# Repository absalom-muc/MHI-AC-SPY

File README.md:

# MHI-AC-SPY

**This repository is no longer maintained and is therefore archived. An improved version including writing to the air conditioner is [here](https://github.com/absalom-muc/MHI-AC-Ctrl)**

The version here should be only used as a demonstration how to program the HW SPI of the ESP8266 for receiving data.

The program reads data (e.g. room temperature, fan status etc.) from a Mitsubishi Heavy Industries (MHI)
air conditioner (AC) via SPI and sends the data via MQTT. The AC is the SPI master and the ESP8266 is the SPI slave.
So far only reading from the AC is supported. (but writing is planned for the future)
The program has a draft status and your input is welcome.
My target is to read and write data with an ESP8266.

# Attention:
You have to open the indoor unit to have access to the SPI. Opening of the indoor unit should be done by 
a qualified professional because faulty handling may cause leakage of water, electric shock or fire!

# Prerequisites:
For use of the program you have to connect your ESP8266 (I use a LOLIN(WEMOS) D1 R2 & mini with 80 MHz) via a
cable connector to your air conditioner. This has to be a split device (separated indoor and outdoor unit).
I assume that all indoor units of the type SRC xx ZS-S are supported. I use the indoor unit SRK 35 ZS-S and the outdoor unit SRC 35 ZS-S.
  
# Installing:

## Hardware:
The ESP8266 is powered from the AC via DC-DC (12V -> 5V) converter
The ESP8266 SPI signals SCL (SPI clock) and MOSI (Master Out Slave In) signals are connected via a voltage divider with the AC. But after gaining some experiences I recommend to use a voltage level shifter instead of a voltage divider.

## Software:
The program uses the [MQTT client library](https://github.com/knolleary/pubsubclient) from Nick O'Leary (knolleary). Thank you Nick - great work!
Please check his GitHub page to see how to install it.
Dwonload MHI-SPI.ino and adapt ssid, password and the MQTT server data in the row MQTTclient.setServer("ds218p", 1883);

# License
This project is licensed under the MIT License - see the LICENSE.md file for details

# Acknowledgments
The coding of the SPI protocol of the AC is a nightmare. Without [rjdekker's MHI2MQTT](https://github.com/rjdekker/MHI2MQTT) I had no chance to understand the protocol! Unfortunatelly rjdekker is not longer active on GitHub. He used an Arduino plus an ESP8266 for his project.

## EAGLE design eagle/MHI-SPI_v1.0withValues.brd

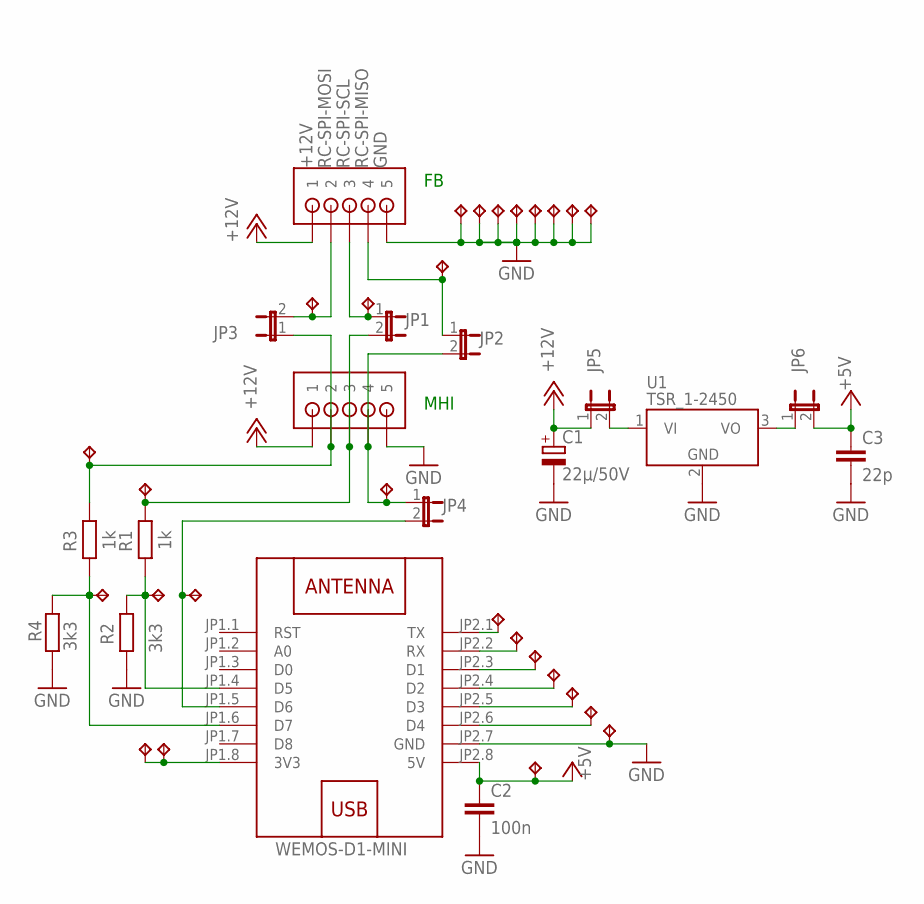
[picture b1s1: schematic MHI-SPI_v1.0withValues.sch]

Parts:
C1: 22µ/50V; E5-10,5
C2: 100n; C025-024X044
C3: 22p; C025-024X044
JP1, JP2, JP3, JP4, JP5, JP6: JP1E; JP1
R1, R3: 1k; VMTA55
R2, R4: 3k3; VMTA55
TP1, TP2, TP3, TP4, TP5, TP6, TP7, TP8, TP9, TP10, TP11, TP12, TP13, TP14, TP15, TP16, TP17, TP18, TP19, TP20, TP21, TP22, TP23, TP24, TP25, TP26, TP27: TPPAD1-13; P1-13
U1: TSR_1-2450; TSR-1
U$1: WEMOS-D1-MINI
U$4, U$5: JST-PH_5-PIN_HEADER; JST_B5B-PH_HEADER

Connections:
+3V3: TP22.TP, TP23.TP, U$1.JP1.8 (3V3)
+5V: C2.1, C3.1, JP6.2, TP21.TP, U$1.JP2.8 (5V)
+12V: C1.+, JP5.1, U$4.P1 (1), U$5.P1 (1)
D1: TP16.TP, U$1.JP2.3 (D1)
D2: TP17.TP, U$1.JP2.4 (D2)
D3: TP18.TP, U$1.JP2.5 (D3)
D4: TP19.TP, U$1.JP2.6 (D4)
GND: C1.-, C2.2, C3.2, R2.2, R4.1, TP1.TP, TP2.TP, TP3.TP, TP4.TP, TP20.TP, TP24.TP, TP25.TP, TP26.TP, TP27.TP, U1.2 (GND), U$1.JP2.7 (GND), U$4.P5 (5), U$5.P5 (5)
MHI-SPI-MISO: JP2.2, JP4.1, TP8.TP, U$5.P4 (4)
MHI-SPI-MOSI: JP3.1, R3.1, TP10.TP, U$5.P2 (2)
MHI-SPI-SCL: JP1.2, R1.1, TP9.TP, U$5.P3 (3)
MISO: JP4.2, TP11.TP, U$1.JP1.5 (D6)
MOSI: R3.2, R4.2, TP13.TP, U$1.JP1.6 (D7)
unnamed: JP6.1, U1.3 (VO)
RC-SPI-MISO: JP2.1, TP5.TP, U$4.P4 (4)
RC-SPI-MOSI: JP3.2, TP7.TP, U$4.P2 (2)
RC-SPI-SCL: JP1.1, TP6.TP, U$4.P3 (3)
RX: TP15.TP, U$1.JP2.2 (RX)
SCK: R1.2, R2.1, TP12.TP, U$1.JP1.4 (D5)
TX: TP14.TP, U$1.JP2.1 (TX)
VI: JP5.2, U1.1 (VI)

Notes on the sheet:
MHI

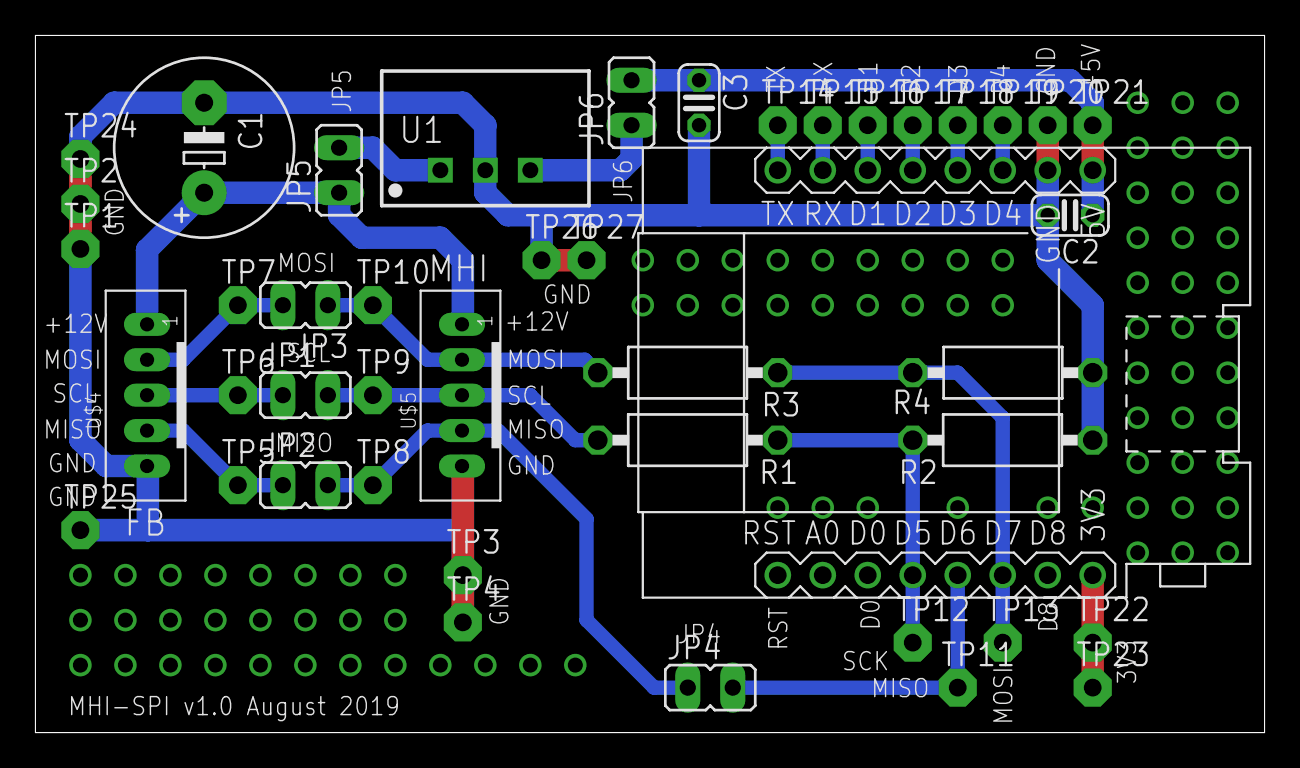
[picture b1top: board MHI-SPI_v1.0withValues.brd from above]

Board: 2 copper layers, 69.4 x 39.4 mm, 44 parts (0 on the bottom side), 21 nets.

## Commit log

2019-10-27 Create MHI-SPI.ino
    Please consider that it is still a draft
2019-10-27 Create tmp
2019-10-28 initial
2019-11-03 see version.md
2019-11-03 name adapted
2019-11-03 values for R2/R4 added
2019-11-11 Update SPI.md
    Vanes and variants added. Temperature setpoint formular corrected.
2019-12-01 formula for Temperature setpoint corrected

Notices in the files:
parts and their libraries:
diy-modules: Released under the Creative Commons Attribution 4.0 International License: http://creativecommons.org/licenses/by/4.0
